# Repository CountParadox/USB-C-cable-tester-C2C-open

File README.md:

# USB C cable tester - C2C caberQU
Can my cable support USB 2.0/3.0/3.1/3.2, power delivery? Is a wire broken?

### Preorder one from Kickstarter 
### https://www.kickstarter.com/projects/electr/c2c-caberqu-usb-c-cable-tester

Tindie link: https://www.tindie.com/products/petl/usb-c-cable-tester-c2c-caberqu/

#### What is it?

The C2C caberQU board applies a voltage to all pins of a cable and measures which ones are connected to the other end. It features LEDs for each of the 24 pins and even shield. So in total 25 LEDs offer all possible combinations for USB-C receptacle pin usage in different modes:

- USB 2.0/1.1
- USB Power Delivery
- USB 3.0/3.1/3.2
- Alternate Mode
- Debug Accessory Mode
- Audio Adapter Accessory Mode

See [Wikipedia](https://en.wikipedia.org/wiki/USB-C#USB-C_receptacle_pin_usage_in_different_modes) to check which pin should be connected to where. 

#### Why did you make it?

The amount of possible USB C cable combinations is endless. If you use the wrong cable, data transmission may be slower than possible or certain devices may not work at all. In the USB C standard, the cable plays an important role and has to advertise itself as such. All of them need to have certain pins connected, some need to be grounded, some need to have resistors attached. 

#### What makes it special?

Unfortunately there is no easy way to extract whether a certain cable can support a certain use case. If a cable has a broken pin, that makes it even worse, due to their unpredictable behavior. The C2C caberQU cable tester solves this once and for all. By flipping the USB connectors, the opposing LEDs for some pins light up due to them not being mirrored. That's on purpose and defined in the USB C standard. The product is sold with one CR2032, the PCB and some basic instructions. The USB C cable is not included. You have to extract the needed pins for your desired usage on your own, unfortunately that can not be done universally for all possible combinations.

No dedicated power supply is needed, all necessary power is supplied via the CR2032 battery.

Please note that if you have a cheaper shipping option I'm gladly using it and refunding you the difference. The item still is a prototype. It is working as intended, but funny quirks and other things are possible. It is not certified and only suited for prototyping. 

If you have any questions, just shoot me a message!

#### What makes this one open? 

The full board and production files are provided, you can edit in kicad, get it mass produced, whatever you want.
Massive thanks to Hank for making this possible with his insane skills in kicad!

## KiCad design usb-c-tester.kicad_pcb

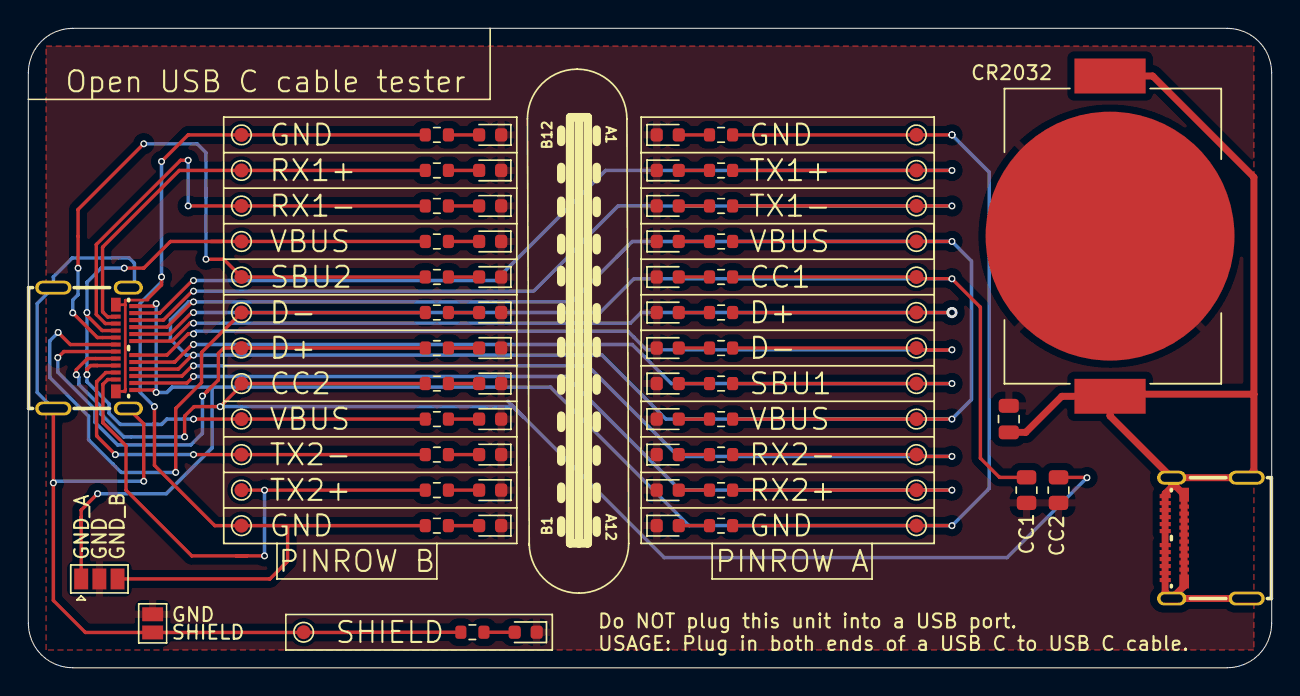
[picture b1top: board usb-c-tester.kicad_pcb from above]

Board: 2 copper layers, 88.9 x 45.7 mm, 83 parts (0 on the bottom side), 48 nets.

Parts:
C1: 1uF; C_0805_2012Metric
G1: BAT-HLD-001-TR; BAT_BAT-HLD-001-TR
J1, J2: 105450-0101
JP1: SolderJumper_3_Open; SolderJumper-3_P1.3mm_Open_Pad1.0x1.5mm
JP2: SolderJumper_2_Open; SolderJumper-2_P1.3mm_Open_Pad1.0x1.5mm
LED1, LED2, LED3, LED4, LED5, LED6, LED7, LED8, LED9, LED10, LED11, LED12, LED13, LED14, LED15, LED16, LED17, LED18, LED19, LED20, LED21, LED22, LED23, LED24, LED25: LED; LED_0603_1608Metric
R1, R2, R3, R4, R5, R6, R7, R8, R9, R10, R11, R12, R13, R14, R15, R16, R17, R18, R19, R20, R21, R22, R23, R24, R25: 100; R_0603_1608Metric
R26, R27: R; R_0805_2012Metric
TP1, TP2, TP3, TP4, TP5, TP6, TP7, TP8, TP9, TP10, TP11, TP12, TP13, TP14, TP15, TP16, TP17, TP18, TP19, TP20, TP21, TP22, TP23, TP24, TP25: TestPoint; TestPoint_Pad_D1.0mm

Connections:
CC1: J2.A5, R5.1, R26.1, TP5.1
CC2: J2.B5, R16.1, R27.1, TP16.1
D1+: J2.A6, R6.1, TP6.1
D1-: J2.A7, R7.1, TP7.1
D2+: J2.B6, R17.1, TP17.1
D2-: J2.B7, R18.1, TP18.1
GND: C1.2, G1.N1, JP1.2, JP2.2, LED1.1, LED2.1, LED3.1, LED4.1, LED5.1, LED6.1, LED7.1, LED8.1, LED9.1, LED10.1, LED11.1, LED12.1, LED13.1, LED14.1, LED15.1, LED16.1, LED17.1, LED18.1, LED19.1, LED20.1, LED21.1, LED22.1, LED23.1, LED24.1, LED25.1, R26.2, R27.2
GND_A: J2.A1, J2.A12, JP1.1, R1.1, R23.1, TP1.1, TP23.1
GND_B: J2.B1, J2.B12, JP1.3, R12.1, R24.1, TP12.1, TP24.1
unnamed: LED1.2, R1.2
unnamed: LED2.2, R2.2
unnamed: LED3.2, R3.2
unnamed: LED4.2, R4.2
unnamed: LED5.2, R5.2
unnamed: LED6.2, R6.2
unnamed: LED7.2, R7.2
unnamed: LED8.2, R8.2
unnamed: LED9.2, R9.2
unnamed: LED10.2, R10.2
unnamed: LED11.2, R11.2
unnamed: LED12.2, R12.2
unnamed: LED13.2, R13.2
unnamed: LED14.2, R14.2
unnamed: LED15.2, R15.2
unnamed: LED16.2, R16.2
unnamed: LED17.2, R17.2
unnamed: LED18.2, R18.2
unnamed: LED19.2, R19.2
unnamed: LED20.2, R20.2
unnamed: LED21.2, R21.2
unnamed: LED22.2, R22.2
unnamed: LED23.2, R23.2
unnamed: LED24.2, R24.2
unnamed: LED25.2, R25.2
RX1+: J2.B11, R21.1, TP21.1
RX1-: J2.B10, R20.1, TP20.1
RX2+: J2.A11, R10.1, TP10.1
RX2-: J2.A10, R9.1, TP9.1
SBU1: J2.A8, R8.1, TP8.1
SBU2: J2.B8, R19.1, TP19.1
SHIELD: J2.S1, J2.S2, J2.S3, J2.S4, JP2.1, R11.1, TP11.1
TX1+: J2.A2, R2.1, TP2.1
TX1-: J2.A3, R3.1, TP3.1
TX2+: J2.B2, R13.1, TP13.1
TX2-: J2.B3, R14.1, TP14.1
VBUS_A: J2.A4, J2.A9, R4.1, R22.1, TP4.1, TP22.1
VBUS_B: J2.B4, J2.B9, R15.1, R25.1, TP15.1, TP25.1
VCC: C1.1, G1.P1, G1.P2, J1.A1, J1.A2, J1.A3, J1.A4, J1.A5, J1.A6, J1.A7, J1.A8, J1.A9, J1.A10, J1.A11, J1.A12, J1.B1, J1.B2, J1.B3, J1.B4, J1.B5, J1.B6, J1.B7, J1.B8, J1.B9, J1.B10, J1.B11, J1.B12, J1.S1, J1.S2, J1.S3, J1.S4

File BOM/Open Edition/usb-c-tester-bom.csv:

Comment,Designator,Footprint,LCSC
1uF,C1,Capacitor_SMD:C_0805_2012Metric,C28323
BAT-HLD-001-TR,G1,BAT_BAT-HLD-001-TR,C964833
105450-0101,"J1,J2",usb-c-tester:105450-0101,C134092
LED,"LED1,LED2,LED3,LED4,LED5,LED6,LED7,LED8,LED9,LED10,LED11,LED12,LED13,LED14,LED15,LED16,LED17,LED18,LED19,LED20,LED21,LED22,LED23,LED24,LED25",LED_SMD:LED_0603_1608Metric,C72038
100,"R1,R2,R3,R4,R5,R6,R7,R8,R9,R10,R11,R12,R13,R14,R15,R16,R17,R18,R19,R20,R21,R22,R23,R24,R25",Resistor_SMD:R_0603_1608Metric,C22775

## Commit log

2022-09-14 Complete kicad files with cpl and bom for jlcpcb
2022-09-14 Open files added
2022-09-14 Open USB C Tester files added
